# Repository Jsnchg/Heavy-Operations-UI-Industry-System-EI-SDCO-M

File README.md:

# Heavy-Operations-UI-Industry-System-EI-SDCO-M

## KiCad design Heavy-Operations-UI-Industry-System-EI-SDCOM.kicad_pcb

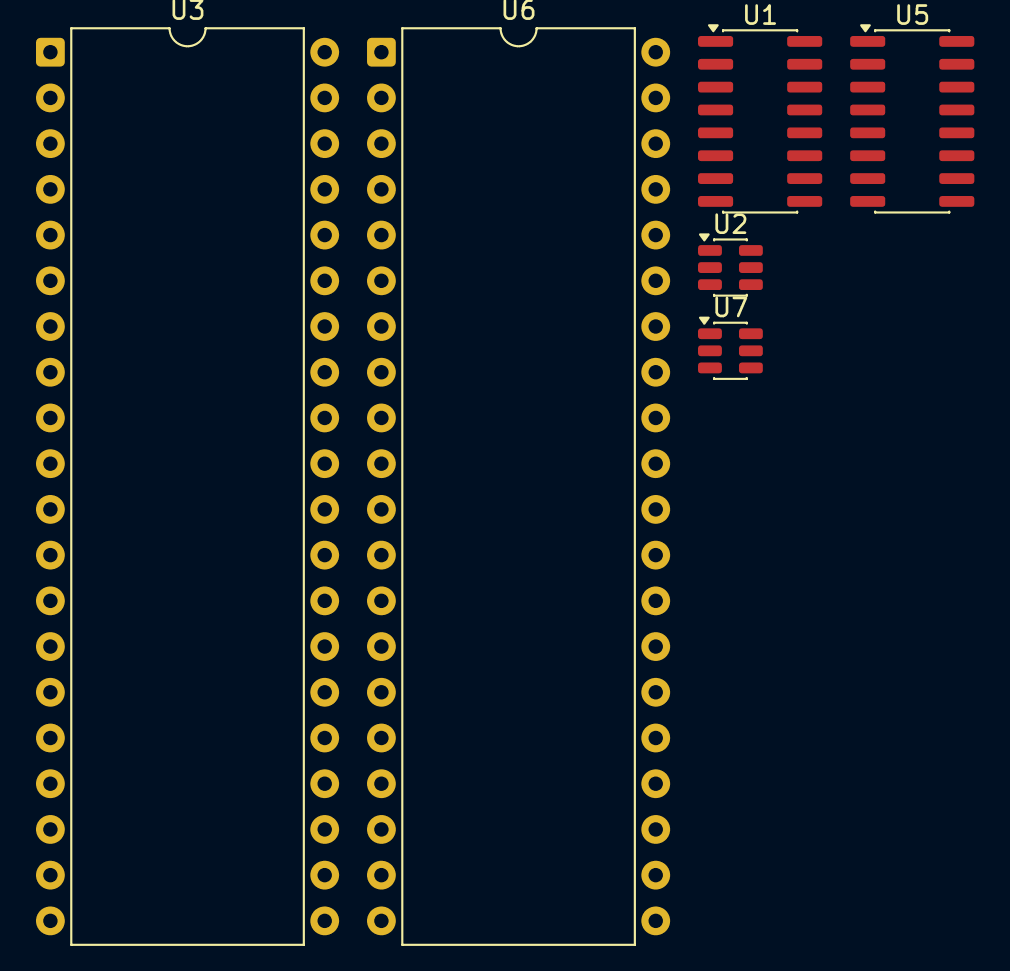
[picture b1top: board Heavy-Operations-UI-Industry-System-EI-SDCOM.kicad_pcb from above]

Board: 2 copper layers, 6 parts (0 on the bottom side), 2 nets, no tracks yet.

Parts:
U1, U5: NCD5702; SOIC-16_3.9x9.9mm_P1.27mm
U2, U7: LM2776; SOT-23-6
U3, U6: 8080; DIP-40_W15.24mm

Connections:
unnamed: U1.12 (VOL), U2.5 (C1+)
unnamed: U5.12 (VOL), U7.5 (C1+)

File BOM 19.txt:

Heavy-Operations-UI-Industry-System-EI-SI
BOM 19

A. Solar DC Optimizer 
1. Solar_Cell
2. NCD5702
3. LM2776
4. D_Schottky_Filled x4
5. GND 
6. 8080
7. NCS211R

B. Solar Microinverter
1. Solar_Cell
2. NCD5702
3. LM2776
4. D_Schottky_Filled x4
5. GND 
6. 8080
7. NCS211R

Note:
Component 3 was added to make the project more unique, all projects have unique components
